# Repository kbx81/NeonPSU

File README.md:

# kbx's Neon Power Supply with ESP32 <!-- omit in TOC -->

This repository contains [KiCad](https://kicad.org) project files for a small power supply PCB for tabletop neon (**real** neon...as opposed to LED "neon") figures/sculptures commonly found on [Etsy](https://etsy.com) and [eBay](https://ebay.com).

This turned out to be, without question, the most challenging and educational electronics project I've ever undertaken.

For more images, please see the [gallery](GALLERY.md). I've also posted a short [video](https://youtu.be/dW0gycuDIJ8) of the neon cactus on [YouTube](https://youtube.com).

## Table of Contents  <!-- omit in TOC -->
- [Preface](#preface)
  - [It Begins](#it-begins)
  - [What's Inside?](#whats-inside)
  - [But One Broke...](#but-one-broke)
  - [I Can Do Better](#i-can-do-better)
  - [Making It Happen](#making-it-happen)
  - [Too Late](#too-late)
- [Introduction](#introduction)
  - [High-Voltage Power Supply & Controller](#high-voltage-power-supply--controller)
  - [ESP32 and Related Peripheral Components](#esp32-and-related-peripheral-components)
- [More Details, Please](#more-details-please)
  - [The Important Bits](#the-important-bits)
    - [Tank Circuit](#tank-circuit)
    - [More Tank Circuit...and Voltage Sensing](#more-tank-circuitand-voltage-sensing)
    - [Current Sensing...and More Voltage Sensing](#current-sensingand-more-voltage-sensing)
  - [Setting Expectations](#setting-expectations)
- [ESPHome Configuration](#esphome-configuration)
- [Legal stuff and License](#legal-stuff-and-license)

## Preface

### It Begins

This project came about as I've had three of these little neon sculptures for quite a while (as in, 20+ years):

It's been something I've wanted to do for a while; that said, I'm glad I waited because I needed every bit of (electronics) knowledge I've amassed over the years to complete it (more on that later).

### What's Inside?

Each one of the neon lamps came with a small cylindrical base and inside of each base was one of these PCBs:

The larger of the three (on the right) was the one that was in the base of the cactus. That said, while they're all physically different, they all more or less work in the same way -- a small power transistor is switched by an oscillator (either a 555 timer or a flyback coil from the transformer) at a high frequency (20-30 kHz), consequently "tickling" a coil on a transformer. The transformer steps up the voltage from the low-voltage power supply (12 volts DC) to a much higher voltage (estimated to be around 2 kV) to light the neon tube.

### But One Broke...

The martini glass's inverter board suffered a (very) premature failure just a couple of months after I'd purchased it. I'm not 100% certain but I have very good reason to believe the failure was due to its transformer. I have a number of reasons to believe this; here is one bit of supporting evidence:

Due to the inexpensive (at the time) nature of it, I never pursued any type of replacement as I thought that, someday, it would make a nice little project to repair it. Well, some time later, here we are and...boy was I right about it being a nice _project_!

### I Can Do Better

While I love and very much appreciate neon lighting in general, I found myself not using any of these lights because of the "broken" one and also because they required me to walk over and manually switch them on and off. I'm wayyyyy too lazy to (remember to) do that. Because of this, they got placed on a shelf and largely forgotten about. I tried repeatedly to find a replacement transformer for the damaged board, but this proved to be more or less impossible. The transformers on the original PCBs have no (useful) markings on them and despite that I tried and tried I just couldn't find anything that I was confident would work. One day I realized that, as an electronics hobbyist, instead of fixing the broken board, I could just design my own. Being a bit of a home automation fanatic, I quickly also realized that they'd be way more enjoyable if they could be remotely switched or even dimmed. Last but certainly not least I realized that I knew just how to make this all happen. I just needed to piece together a little puzzle...

### Making It Happen

My goal was to draw up a PCB that would fit into all of the original bases. Given that the bases contained mostly empty space, this wasn't terribly challenging. The original PCB in the cactus's base was designed such that the power jack and switch were positioned to be exposed directly through the back of the base; the other PCBs had their power jack and switch mounted into the base elsewhere and wires were used to attach these to the PCB. As such, the physical layout of the PCB was less important for these.

As you can see in the picture at the top of this section, each length of neon tube is terminated into a small plastic "plug" that slides into a "socket" recessed into the base. All of these are the same size and, on the bottom of the plug, two terminals are exposed. These contact spring terminals when the neon is inserted into the base -- hence the two spring terminals (surprise -- they're battery contacts!) you see in the middle of the PCBs I designed.

It turns out that the physical design and layout was the easy part...for several reasons...

Physical requirements/constraints aside, I also wanted to be able to remotely control and dim the neon lights. Having worked with them quite a bit in other projects, I knew that the [ESP32](https://www.espressif.com/en/products/socs/esp32) was more than sufficiently equipped to accommodate this -- the question was, how do you get a little 3.3-volt microcontroller to control a 2,000-volt power supply? It turns out that it's not terribly difficult...kind of. You just need the right parts and, at least a few years ago, these were pretty common.

After much researching and digging, I learned about ICs known as "CCFL controllers". These parts are specifically designed to manage these types of light sources and to allow control of them via a microcontroller. Neat! I came across the [TPS68000](https://www.ti.com/product/TPS68000) as I was trying to find an appropriately-rated transformer for this application. TI had an evaluation board for the [TPS68000](https://www.ti.com/product/TPS68000) that featured the Coilcraft [FA2786-BL](https://www.coilcraft.com/en-us/products/transformers/power-transformers/ccfl-transformers/fa2786/). I ordered a few of these and began testing them -- they appeared to work great for this application so I moved forward with a design based on the evaluation board for these parts.

### Too Late

Here's the catch -- I'm at least ten years (at the time of this writing) late to taking on this project. You see, right now, LEDs are replacing _every_ other type of light source. Before LEDs could light...anything...discharge lighting (neon, CCFLs, etc.) was much more common...and so were the electronics to make these things work. While none of this is gone completely just yet, it's becoming more and more difficult to find parts to make these types of light sources work with the type of control I wanted.

I had to order the [TPS68000](https://www.ti.com/product/TPS68000) ICs from someone on [eBay](https://ebay.com). They don't appear to be obsolete...yet...but I expect they will be marked as such soon, probably within the next year or two. An alternative might be the [MAX8722C](https://www.maximintegrated.com/en/products/power/MAX8722C.html) as it appears to be quite similar; that said, I haven't tested it, but I did order a few to have on-hand. Side note: the [MAX8722C's](https://www.maximintegrated.com/en/products/power/MAX8722C.html) [reference manual](https://datasheets.maximintegrated.com/en/ds/MAX8722C.pdf) ultimately proved to be _much_ more insightful than the manual for the [TPS68000](https://www.ti.com/product/TPS68000).

The [FA2786-BL](https://www.coilcraft.com/en-us/products/transformers/power-transformers/ccfl-transformers/fa2786/) was only available for purchase directly from Coilcraft; I'm also not convinced it will be produced for much longer. I guess time will tell.

With all of this in mind, I put aside my concerns around designing a board based around soon-to-be-obsolete parts and drew up a schematic and PCB. If I'm going to do this, it needs to be now.

## Introduction

I've designed this circuit to power the neon sculptures shown above. It allows remotely switching and dimming of the neon via the [ESP32](https://www.espressif.com/en/products/socs/esp32); I used this part with [ESPHome](https://esphome.io) in mind for the firmware. It's a perfect fit!

The circuit consists of two main parts:
 - High-voltage power supply & [TPS68000](https://www.ti.com/product/TPS68000) controller
 - [ESP32](https://www.espressif.com/en/products/socs/esp32) and related peripheral components

### High-Voltage Power Supply & Controller

The high-voltage power supply is the heart of this design. Without it, the neon won't light.

As the [TPS68000](https://www.ti.com/product/TPS68000) is the center of this part, the majority of the design comes straight out of its [reference manual](https://www.ti.com/lit/ds/symlink/tps68000.pdf) -- or, more specifically, the manual for the [TPS68000EVM-202 evaluation board](https://www.ti.com/lit/ug/slvu206/slvu206.pdf). That said, the design had to be tuned somewhat to accommodate the characteristics of the longer, larger-diameter neon tubes. More on this later.

### ESP32 and Related Peripheral Components

There's not much to be said about this part -- the board has a footprint for an [ESP32-WROOM](https://www.espressif.com/en/products/modules/esp32)-series module and a few components to support it, such as power and status LEDs, a 3.3-volt regulator and appropriate pull-up/down resistors. There is also a header through which the microcontroler can be flashed with its firmware. Appropriate GPIO pins are connected to the [TPS68000](https://www.ti.com/product/TPS68000) to allow switching on/off of the neon as well as dimming (via the ESP32's DAC and/or PWM). The [TPS68000's](https://www.ti.com/product/TPS68000) `fault` line is also connected so that the ESP32 can be aware of faults on the high-voltage side.

## More Details, Please

As I said earlier, this turned out to be the most challenging and educational electronics project I've ever undertaken. Let's talk about that.

At this point, I've done plenty of work with the [ESP32](https://www.espressif.com/en/products/socs/esp32) -- that wasn't the challenging part. The [TPS68000](https://www.ti.com/product/TPS68000) is by far and away where the challenge came in. Prior to this project, I'd never worked with LC (inductance-capacitance) circuits before; I quickly realized that I had a lot to learn to get this (mostly) right.

I designed a test PCB to try out the suggested full-bridge configuration to drive the transformer. This worked out great as an initial proof-of-concept for the design -- I just wanted to see this work as it wasn't something I had tried before. I wasn't sure about heat, frequency, power draw, etc. and I wanted to get a feel for this before I risked blowing up a now-hard-to-get [TPS68000](https://www.ti.com/product/TPS68000). Once I saw the design working, I moved on to the next step/phase of the design.

The [TPS68000](https://www.ti.com/product/TPS68000) is a clever little IC. I read and felt like I understood its [reference manual](https://www.ti.com/lit/ds/symlink/tps68000.pdf), but until I finally got to physically working with it, I didn't quite realize just what I needed to do. Some of my struggle was due to my lack of experience with tuning feedback circuits, some of it was due to the somewhat different characteristics of the neon tubes (as opposed to a plain CCFL tube).

### The Important Bits

Let's look at some of the speed bumps I encountered as I was working through understanding the various aspects of the design.

#### Tank Circuit

The low-voltage side of the transformer has its coil in series with a capacitor. This forms a series-resonant tank circuit. There are plenty of other sites around the internet to explain these in detail, so I won't go into that here; what's important to know for this application is that the values of the capacitor and inductor (which, in this case, is one of the transformer's coils) define a resonant frequency. We do **not** want the oscillator to be operating _at_ this frequency -- it should be above it, ideally at least two times the resonant frequency. The [TPS68000](https://www.ti.com/product/TPS68000) needs to be configured accordingly.

#### More Tank Circuit...and Voltage Sensing

On the high-voltage side of the transformer, there is a capacitive divider which allows the [TPS68000](https://www.ti.com/product/TPS68000) to sense (and consequently regulate) the voltage there. The values of these two capacitors define both the voltage that the [TPS68000](https://www.ti.com/product/TPS68000) will try to regulate/maintain as well as the parallel-resonant frequency of the circuit; this frequency is important _before_ the (neon) lamp strikes (in other words, when it is nothing more than an open circuit). As the [TPS68000's](https://www.ti.com/product/TPS68000) [reference manual](https://www.ti.com/lit/ds/symlink/tps68000.pdf) mentions, when the controller is enabled, it will start its oscillator at two times the configured frequency. It will sweep the frequency from there down to as low as one-half of the configured frequency as it tries to strike the lamp. What's important here is that it needs to pass through that parallel-resonant frequency in order to produce the maximum possible voltage across the lamp to ensure that it strikes. If the values of these capacitors don't allow that or if the configured frequency isn't quite high enough, the lamp may not strike reliably, if at all.

#### Current Sensing...and More Voltage Sensing

In addition to the frequency-related items described above, voltages that appear on the [TPS68000's](https://www.ti.com/product/TPS68000) `CSEN` and `VSEN` inputs are also critically important. The [reference manual](https://www.ti.com/lit/ds/symlink/tps68000.pdf) contains screen captures from a scope; it doesn't say much about these but they illustrate what the voltages _should_ look like on these inputs. Don't deviate from these -- if the voltage on either pin is too high, the device will either shut down or regulation will suffer, typically resulting in the transformer "whistling". The capacitors that form the voltage divider on the high voltage side as well as the shunt resistors on either side of the coil/lamp _must_ be chosen with extreme care and it should be noted that these may not be the same from lamp to lamp. For example, in general, I've found that neon lamps with a shorter overall tube length typically require a smaller shunt resistor. In addition, for a given pair of values for the capacitors that form the divider, a shorter overall tube length will result in a smaller voltage appearing on `VSEN`. It may or may not be necessary to compensate for this by adjusting the values of these capacitors.

### Setting Expectations

This is not a circuit you can just build on a board and be done with it...unless you were mass-producing them to be used with a single specific (CCFL) lamp. I've pinned down some component values that tend to work well as a starting point, but in this application, I've found that each board I build needs to be tuned to some extent for the lamp it will be paired with.

With that in mind, I can tell you that an oscilloscope is almost definitely necessary to perform this process correctly. It might be possible with a (good) DMM alone but...good luck. If you plan to build one of these, you should also plan to do some post-build tuning of the circuit. Measure at each of the test points I've put on the board and compare them with the scope captures shown in the [reference manual](https://www.ti.com/lit/ds/symlink/tps68000.pdf). If they're more than about a half of a volt off, you probably need to tweak some resistor and/or capacitor values. In some cases, bumping the frequency up or down a bit (by maybe 1 kHz or so) may help. That said, through lots and lots of experimenting I've found frequencies around 35 kHz or so seem to play best with these types of neon tubes coupled with this circuit. Your mileage may vary.

Overall, the math required for the [TPS68000](https://www.ti.com/product/TPS68000) is a bit involved. A calculator alone is not enough -- you really need a [spreadsheet](https://docs.google.com/spreadsheets/d/1VhNCAI64YPz2V6RbbLRd5rNgBKweANUHgwTCD990pUk/edit?usp=sharing) to hash it all out. Mine is a bit messy and probably isn't perfect but nonetheless it was quite helpful as I fine-tuned my boards. If you build one of these boards and use it, I hope it proves helpful for you, too.

If you are particularly interested in more specifics of the circuit's operation and/or related formulas, I highly recommend taking a look at the [MAX8722C's](https://www.maximintegrated.com/en/products/power/MAX8722C.html) [reference manual](https://datasheets.maximintegrated.com/en/ds/MAX8722C.pdf). It is a very similar controller and its manual is easily an order of magnitude better than the [reference manual](https://www.ti.com/lit/ds/symlink/tps68000.pdf) for the [TPS68000](https://www.ti.com/product/TPS68000), at least as it relates to the explanation of the circuit's operation and mathematical models/representations.

## ESPHome Configuration

I've created a separate repository for my [ESPHome](https://esphome.io) [configurations](https://github.com/kbx81/esphome-configs); configurations I'm using with this board for my various neon lamps are located there.

## Legal stuff and License

Everything you see here is provided to you free of charge. You are free to use it however you please within the constraints of the license -- but you do so at your own risk. This circuit produces a high voltage that could be lethal -- you must use extreme care when handling and testing! I accept absolutely no liability if you cause damage to your property, person, or any other hardware you choose to connect to this device.

The circuit schematic, PCB and enclosures found here are licensed under the [Creative Commons Attribution-ShareAlike 4.0 International License](http://creativecommons.org/licenses/by-sa/4.0/).

_Thanks for visiting!_

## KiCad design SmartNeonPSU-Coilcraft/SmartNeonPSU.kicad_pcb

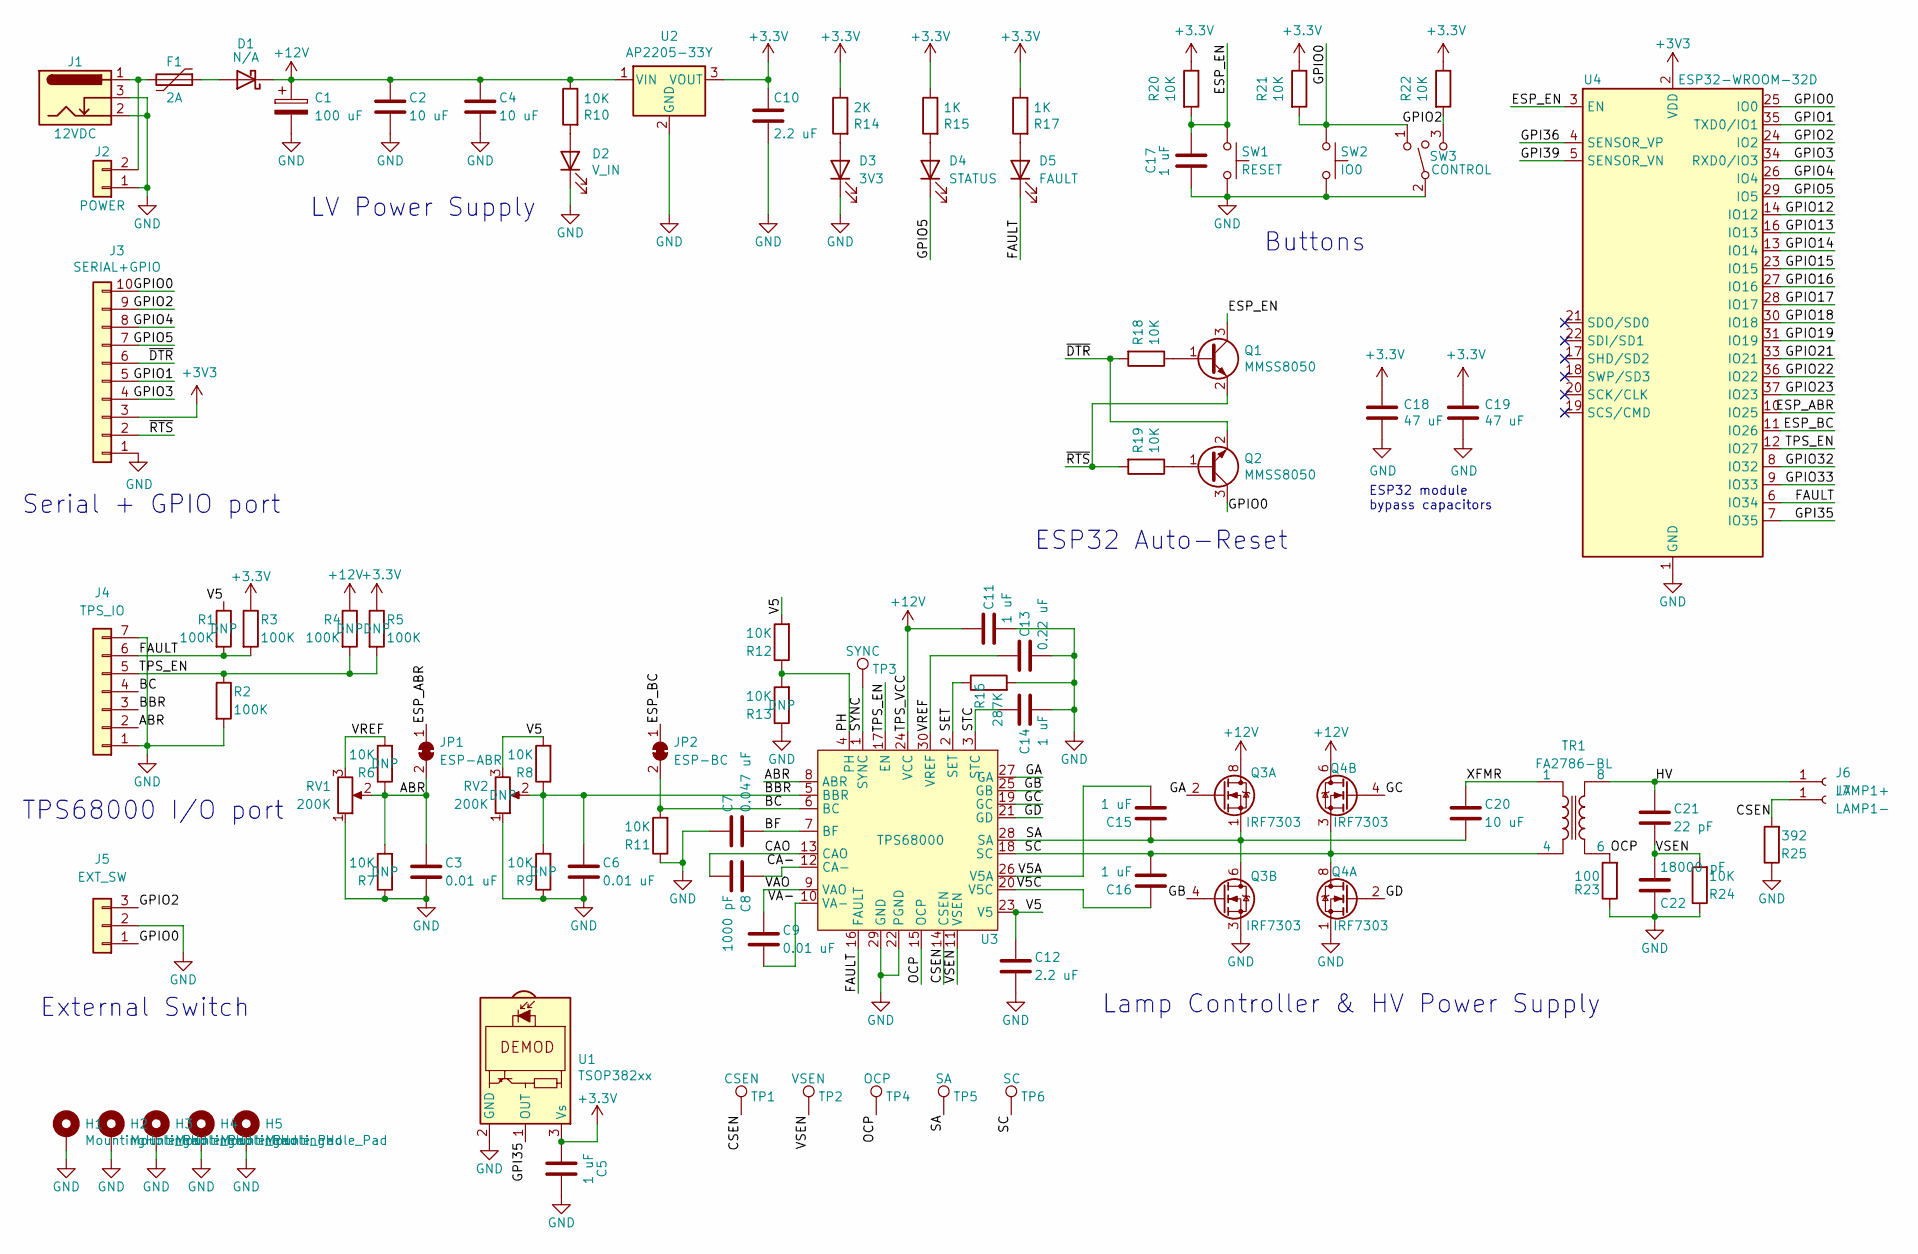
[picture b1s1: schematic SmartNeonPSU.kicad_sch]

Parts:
C1: 100 uF; CP_Elec_8x6.9; MPN1 25SVF100M
C2, C4, C20: 10 uF; C_0805_2012Metric; MPN1 C2012X5R1V106K085AC
C3, C6, C9: 0.01 uF; C_0805_2012Metric; MPN1 CC0805JRX7R8BB103
C5, C11, C14, C15, C16, C17: 1 uF; C_0805_2012Metric; MPN1 C2012X5R1E105M125AA
C7: 0.047 uF; C_0805_2012Metric; MPN1 CC0805JRX7R9BB473
C8: 1000 pF; C_0805_2012Metric; MPN1 CC0805KRX7R9BB102
C10, C12: 2.2 uF; C_0805_2012Metric; MPN1 C2012X5R1E225M125AC
C13: 0.22 uF; C_0805_2012Metric; MPN1 CC0805JRX7R7BB224
C18, C19: 47 uF; C_0805_2012Metric; MPN1 GRM21BR60J476ME15L
C21: 22 pF; C_1808_4520Metric_Slot; MPN1 C4520C0G3F220K
C22: 18000 pF; C_0805_2012Metric; MPN1 CC0805KRX7R9BB183
D1: N/A; D_SOD-123F; MPN1 MBR230S1F-7
D2: V_IN; LED_0805_2012Metric; MPN1 LSM0805543V
D3: 3V3; LED_0805_2012Metric; MPN1 LSM0805543V
D4: STATUS; LED_0805_2012Metric; MPN1 APT2012EC
D5: FAULT; LED_0805_2012Metric; MPN1 APT2012EC
F1: 2A; Fuse_2920_7451Metric; MPN1 2920L030DR
H1, H2, H3, H4, H5: MountingHole_Pad; MountingHole_3.2mm_M3_Pad_Via
J1: 12VDC; BarrelJack_Horizontal
J2: POWER; PinSocket_1x02_P2.54mm_Vertical
J3: SERIAL+GPIO; PinSocket_1x10_P2.54mm_Vertical
J4: TPS_IO; PinSocket_1x07_P2.54mm_Vertical
J5: EXT_SW; PinSocket_1x03_P2.54mm_Vertical
J6: LAMP1+; SpringContact_9.9mm_5mm
J7: LAMP1-; SpringContact_9.9mm_5mm
JP1: ESP-ABR; SolderJumper-2_P1.3mm_Bridged_RoundedPad1.0x1.5mm
JP2: ESP-BC; SolderJumper-2_P1.3mm_Bridged_RoundedPad1.0x1.5mm
Q1, Q2: MMSS8050; SOT-23; MPN1 MMSS8050
Q3, Q4: IRF7303; SOIC-8_3.9x4.9mm_P1.27mm; MPN1 IRF7303TRPBF
R1, R2, R3, R4, R5: 100K; R_0805_2012Metric; MPN1 RC0805FR-07100KL
R6, R7, R8, R9, R10, R11, R12, R13, R18, R19, R20, R21, R22, R24: 10K; R_0805_2012Metric; MPN1 RC0805FR-0710KL
R14: 2K; R_0805_2012Metric; MPN1 RC0805FR-072KL
R15, R17: 1K; R_0805_2012Metric; MPN1 RC0805FR-071KL
R16: 287K; R_0805_2012Metric; MPN1 RC0805FR-07287KL
R23: 100; R_0805_2012Metric; MPN1 RC0805FR-07100RL
R25: 392; R_0805_2012Metric; MPN1 RC0805FR-07392RL
RV1, RV2: 200K; Potentiometer_Bourns_3266W_Vertical; MPN1 3266W-1-204LF
SW1: RESET; SW_Push_1P1T_NO_CK_KMR2; MPN1 KMR221GLFS
SW2: IO0; SW_Push_1P1T_NO_CK_KMR2; MPN1 KMR221GLFS
SW3: CONTROL; E-Switch_R1966A‎_7mm_RA; MPN1 R1966IBLKBLKHR
TP1: CSEN; TestPoint_Pad_D1.0mm
TP2: VSEN; TestPoint_Pad_D1.0mm
TP3: SYNC; TestPoint_Pad_D1.0mm
TP4: OCP; TestPoint_Pad_D1.0mm
TP5: SA; TestPoint_Pad_D1.0mm
TP6: SC; TestPoint_Pad_D1.0mm
TR1: FA2786-BL
U1: TSOP382xx; Vishay_MINICAST-3Pin; MPN1 TSOP38238
U2: AP2205-33Y; SOT-89-3; MPN1 AP2205-33Y
U3: TPS68000; TSSOP-30_4.4x7.8mm_P0.5mm; MPN1 TPS68000DBT
U4: ESP32-WROOM-32D; ESP32-WROOM-32; MPN1 ESP32-WROOM-32D

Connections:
+12V: C1.1, C2.1, C4.1, C11.1, D1.1 (K), Q3.7 (D), Q3.8 (D), Q4.5 (D), Q4.6 (D), R4.1, R10.1, U2.1 (VIN), U3.24 (VCC)
/ABR: C3.1, J4.2, JP1.2 (B), R6.1, R7.2, RV1.2, U3.8 (ABR)
/BBR: C6.1, J4.3, R8.1, R9.2, RV2.2, U3.5 (BBR)
/BC: J4.4, JP2.2 (B), R11.2, U3.6 (BC)
/BF: C7.2, U3.7 (BF)
/CA-: C8.1, U3.12 (CA-)
/CAO: C8.2, U3.13 (CAO)
/CSEN: J7.1, R25.2, TP1.1, U3.14 (CSEN)
/ESP_ABR: JP1.1 (A), U4.10 (IO25)
/ESP_BC: JP2.1 (A), U4.11 (IO26)
/ESP_EN: C17.1, Q1.3 (C), R20.2, SW1.1, U4.3 (EN)
/FAULT: D5.1 (K), J4.6, R1.2, R3.2, U3.16 (FAULT), U4.6 (IO34)
/GA: Q3.2 (G), U3.27 (GA)
/GB: Q3.4 (G), U3.25 (GB)
/GC: Q4.4 (G), U3.19 (GC)
/GD: Q4.2 (G), U3.21 (GD)
/GPI35: U1.1 (OUT), U4.7 (IO35)
/GPI36: U4.4 (SENSOR_VP)
/GPI39: U4.5 (SENSOR_VN)
/GPIO0: J3.10, J5.1, Q2.3 (C), R21.2, SW2.1, SW3.1, U4.25 (IO0)
/GPIO1: J3.5, U4.35 (TXD0/IO1)
/GPIO2: J3.9, J5.3, R22.2, SW3.3, U4.24 (IO2)
/GPIO3: J3.4, U4.34 (RXD0/IO3)
/GPIO4: J3.8, U4.26 (IO4)
/GPIO5: D4.1 (K), J3.7, U4.29 (IO5)
/GPIO12: U4.14 (IO12)
/GPIO13: U4.16 (IO13)
/GPIO14: U4.13 (IO14)
/GPIO15: U4.23 (IO15)
/GPIO16: U4.27 (IO16)
/GPIO17: U4.28 (IO17)
/GPIO18: U4.30 (IO18)
/GPIO19: U4.31 (IO19)
/GPIO21: U4.33 (IO21)
/GPIO22: U4.36 (IO22)
/GPIO23: U4.37 (IO23)
/GPIO32: U4.8 (IO32)
/GPIO33: U4.9 (IO33)
/HV: C21.1, J6.1, TR1.8
/OCP: R23.2, TP4.1, TR1.6, U3.15 (OCP)
/PH: R12.1, R13.2, U3.4 (PH)
/SA: C15.1, C20.2, Q3.1 (S), Q3.5 (D), Q3.6 (D), TP5.1, U3.28 (SA)
/SC: C16.2, Q4.3 (1), Q4.7 (D), Q4.8 (D), TP6.1, TR1.4, U3.18 (SC)
/SET: R16.1, U3.2 (SET)
/STC: C14.2, U3.3 (STC)
/SYNC: TP3.1, U3.1 (SYNC)
/TPS_EN: J4.5, R2.1, R4.2, R5.2, U3.17 (EN), U4.12 (IO27)
/V5: C12.1, R1.1, R8.2, R12.2, RV2.3, U3.23 (V5)
/V5A: C15.2, U3.26 (V5A)
/V5C: C16.1, U3.20 (V5C)
/VA-: C9.2, U3.10 (VA-)
/VAO: C9.1, U3.9 (VAO)
/VREF: C13.1, R6.2, RV1.3, U3.30 (VREF)
/VSEN: C21.2, C22.1, R24.2, TP2.1, U3.11 (VSEN)
/XFMR: C20.1, TR1.1
/~DTR: J3.6, Q2.2 (E), R18.2
/~RTS: J3.2, Q1.2 (E), R19.2
GND: C1.2, C2.2, C3.2, C4.2, C5.1, C6.2, C7.1, C10.2, C11.2, C12.2, C13.2, C14.1, C17.2, C18.2, C19.2, C22.2, D2.1 (K), D3.1 (K), H1.1, H2.1, H3.1, H4.1, H5.1, J1.2, J1.3, J2.1, J3.1, J4.1, J4.7, J5.2, Q3.3 (1), Q4.1 (S), R2.2, R7.1, R9.1, R11.1, R13.1, R16.2, R23.1, R24.1, R25.1, RV1.1, RV2.1, SW1.2, SW2.2, SW3.2, U1.2 (GND), U2.2 (GND), U3.22 (PGND), U3.29 (GND), U4.1 (GND), U4.15 (GND), U4.38 (GND), U4.39 (GND)
unnamed: D1.2 (A), F1.1
unnamed: D2.2 (A), R10.2
unnamed: D3.2 (A), R14.2
unnamed: D4.2 (A), R15.2
unnamed: D5.2 (A), R17.2
unnamed: F1.2, J1.1, J2.2
unnamed: Q1.1 (B), R18.1
unnamed: Q2.1 (B), R19.1

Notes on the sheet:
ESP32 module bypass capacitors
Lamp Controller & HV Power Supply
TPS68000 I/O port
Serial + GPIO port
ESP32 Auto-Reset
LV Power Supply
Buttons
External Switch

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
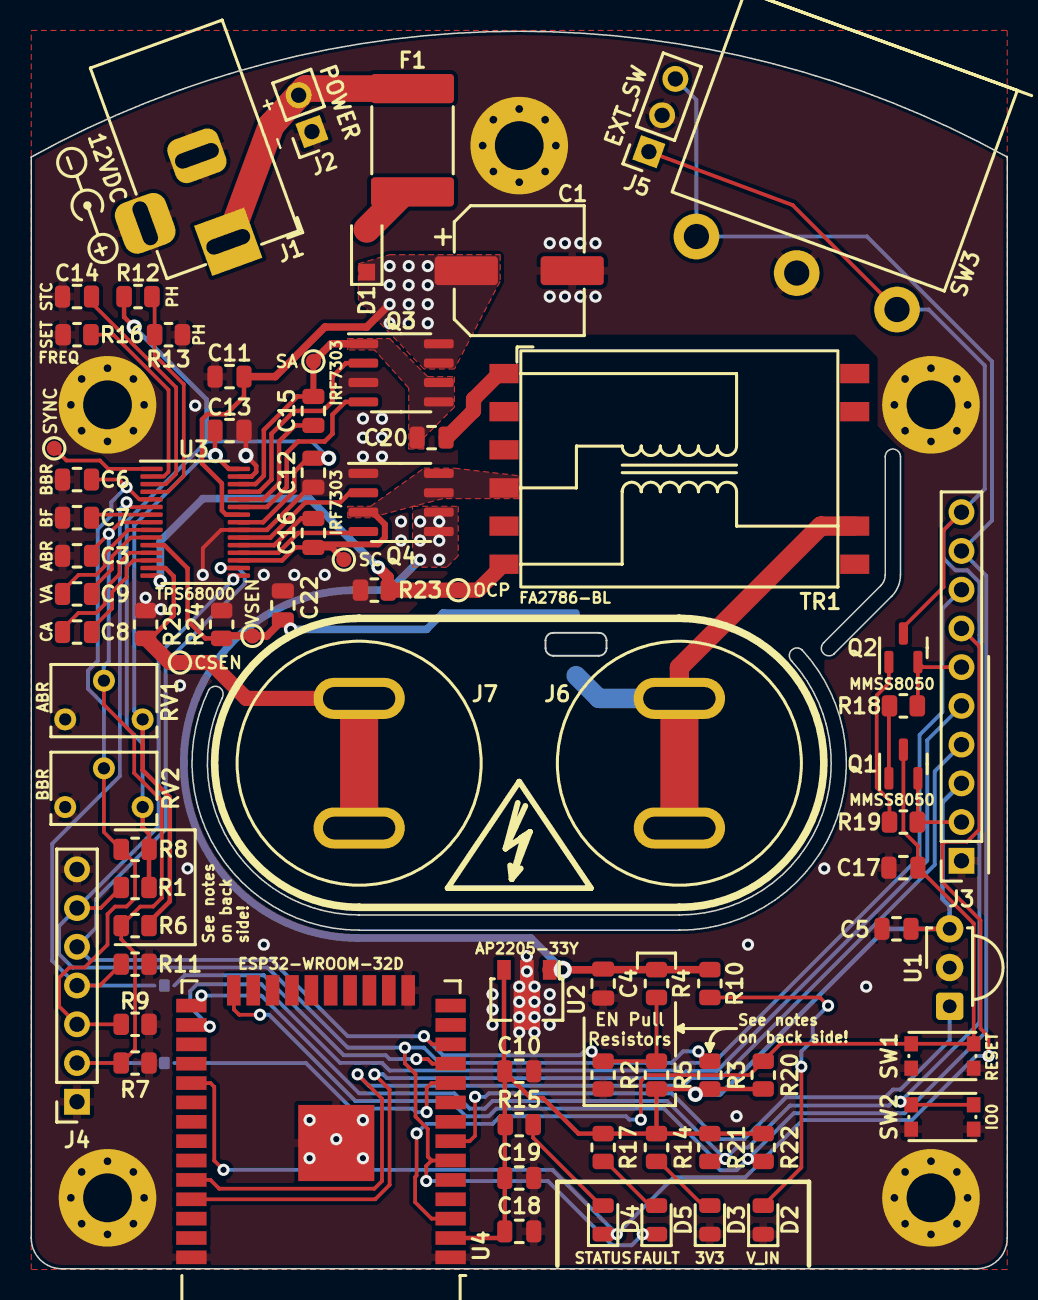
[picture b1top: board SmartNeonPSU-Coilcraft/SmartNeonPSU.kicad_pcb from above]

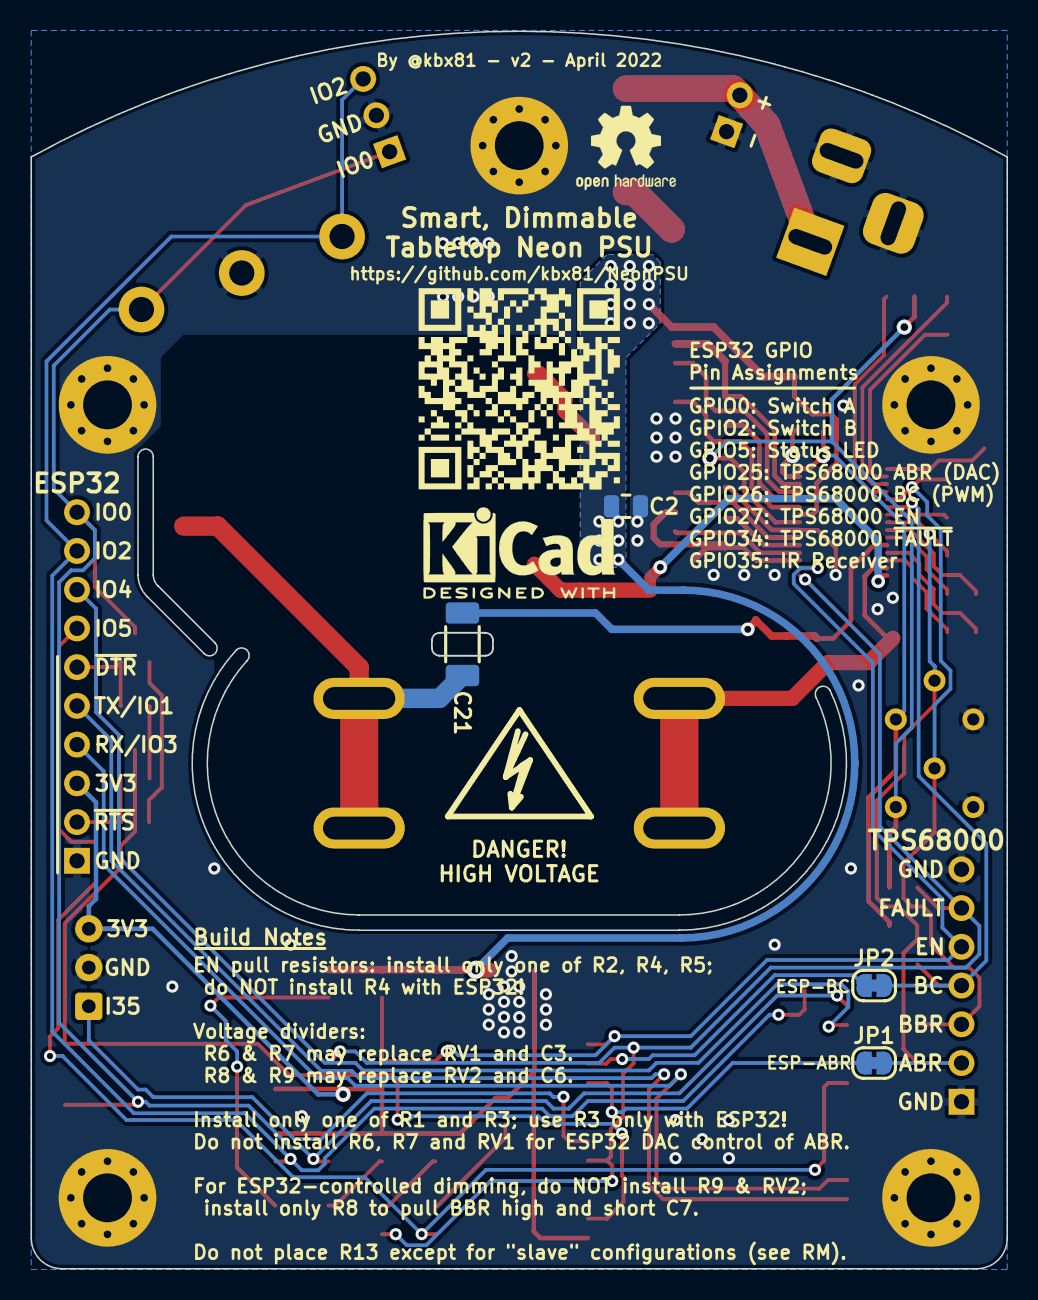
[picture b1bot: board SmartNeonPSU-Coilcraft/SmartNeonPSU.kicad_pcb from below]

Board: 2 copper layers, 64.0 x 81.1 mm, 88 parts (5 on the bottom side), 52 nets.

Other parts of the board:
QR*****: NeonPSU_QR

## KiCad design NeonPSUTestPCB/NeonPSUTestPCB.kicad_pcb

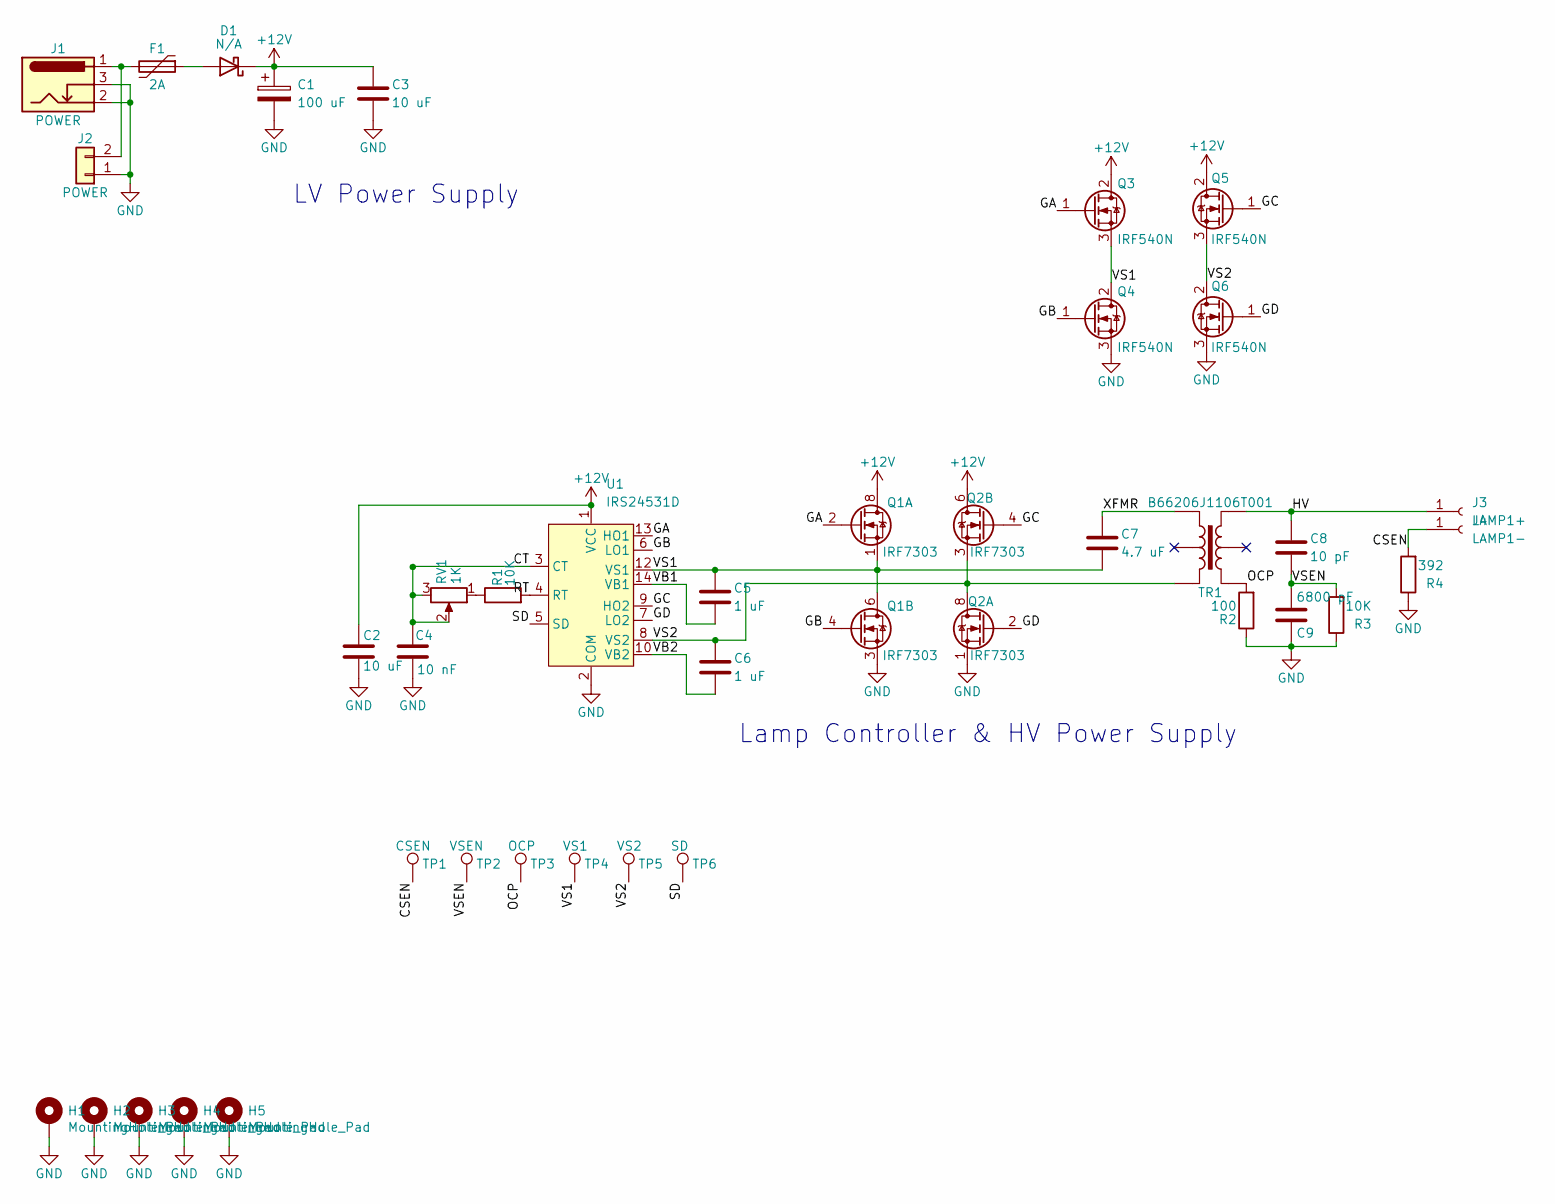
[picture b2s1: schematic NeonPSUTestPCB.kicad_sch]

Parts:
C1: 100 uF; CP_Elec_5x5.3; MPN1 25SVF100M
C2, C3: 10 uF; C_0805_2012Metric; MPN1 C2012X5R1V106K085AC
C4: 10 nF; C_0805_2012Metric
C5, C6: 1 uF; C_0805_2012Metric; MPN1 C2012X5R1E105M125AA
C7: 4.7 uF; C_0805_2012Metric; MPN1 C2012X7R1H475K125AE
C8: 10 pF; C_1808_4520Metric_Slot; MPN1 C4520C0G3F100F
C9: 6800 pF; C_0805_2012Metric; MPN1 CC0805KRX7R9BB682
D1: N/A; D_SOD-123F; MPN1 MBR230S1F-7
F1: 2A; Fuse_2920_7451Metric; MPN1 2920L030DR
H1, H2, H3, H4, H5: MountingHole_Pad; MountingHole_2.2mm_M2_Pad_Via
J1: POWER; BarrelJack_Horizontal
J2: POWER; PinSocket_1x02_P2.54mm_Vertical
J3: LAMP1+; SpringContact_9.9mm_5mm
J4: LAMP1-; SpringContact_9.9mm_5mm
Q1, Q2: IRF7303; SOIC-8_3.9x4.9mm_P1.27mm; MPN1 IRF7303TRPBF
Q3, Q4, Q5, Q6: IRF540N; TO-220-3_Vertical
R1, R3: 10K; R_0805_2012Metric; MPN1 RC0805FR-0710KL
R2: 100; R_0805_2012Metric; MPN1 RC0805FR-07100RL
R4: 392; R_0805_2012Metric; MPN1 RC0805FR-07392RL
RV1: 1K; Potentiometer_Bourns_3266W_Vertical
TP1: CSEN; TestPoint_Pad_D1.0mm
TP2: VSEN; TestPoint_Pad_D1.0mm
TP3: OCP; TestPoint_Pad_D1.0mm
TP4: VS1; TestPoint_Pad_D1.0mm
TP5: VS2; TestPoint_Pad_D1.0mm
TP6: SD; TestPoint_Pad_D1.0mm
TR1: B66206J1106T001; MPN1 B66206J1106T001
U1: IRS24531D; SOIC-14_3.9x8.7mm_P1.27mm; MPN1 IRS24531DSPBF

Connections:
+12V: C1.1, C2.1, C3.1, D1.1 (K), Q1.7 (D), Q1.8 (D), Q2.5 (D), Q2.6 (D), Q3.2 (D), Q5.2 (D), U1.1 (VCC)
/CSEN: J4.1, R4.2, TP1.1
/CT: C4.1, RV1.2, RV1.3, U1.3 (CT)
/GA: Q1.2 (G), Q3.1 (G), U1.13 (HO1)
/GB: Q1.4 (G), Q4.1 (G), U1.6 (LO1)
/GC: Q2.4 (G), Q5.1 (G), U1.9 (HO2)
/GD: Q2.2 (G), Q6.1 (G), U1.7 (LO2)
/HV: C8.1, J3.1, TR1.6
/OCP: R2.2, TP3.1, TR1.4
/RT: R1.2, U1.4 (RT)
/SD: TP6.1, U1.5 (SD)
/VB1: C5.2, U1.14 (VB1)
/VB2: C6.2, U1.10 (VB2)
/VS1: C5.1, C7.2, Q1.1 (S), Q1.5 (D), Q1.6 (D), Q3.3 (S), Q4.2 (D), TP4.1, U1.12 (VS1)
/VS2: C6.1, Q2.3 (1), Q2.7 (D), Q2.8 (D), Q5.3 (S), Q6.2 (D), TP5.1, TR1.3, U1.8 (VS2)
/VSEN: C8.2, C9.1, R3.2, TP2.1
/XFMR: C7.1, TR1.1
GND: C1.2, C2.2, C3.2, C4.2, C9.2, H1.1, H2.1, H3.1, H4.1, H5.1, J1.2, J1.3, J2.1, Q1.3 (1), Q2.1 (S), Q4.3 (S), Q6.3 (S), R2.1, R3.1, R4.1, U1.2 (COM)
unnamed: D1.2 (A), F1.1
unnamed: F1.2, J1.1, J2.2
unnamed: R1.1, RV1.1

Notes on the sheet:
Lamp Controller & HV Power Supply
LV Power Supply

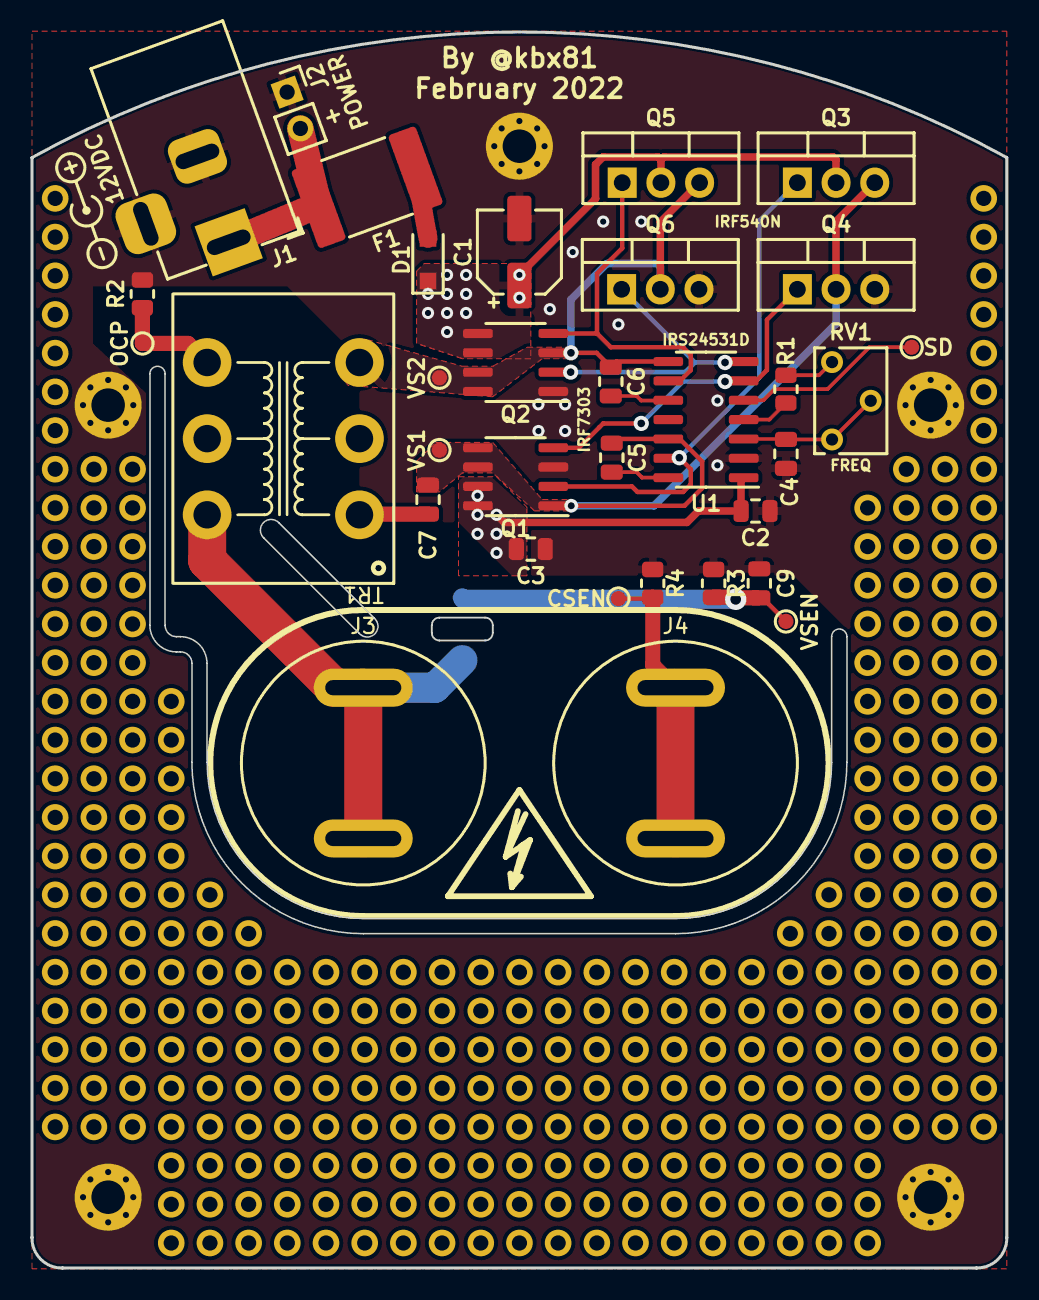
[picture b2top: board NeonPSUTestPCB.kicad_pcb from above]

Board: 2 copper layers, 64.0 x 81.1 mm, 39 parts (1 on the bottom side), 21 nets.

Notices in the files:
README.md:
Everything you see here is provided to you free of charge. You are free to use it however you please within the constraints of the license -- but you do so at your own risk. This circuit produces a high voltage that could be lethal -- you must use extreme care when handling and testing! I accept absolutely no liability if you cause damage to your property, person, or any other hardware you choose to connect to this device.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
Creative Commons License badge
